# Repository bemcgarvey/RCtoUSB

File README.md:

# RCtoUSB - Wireless Joystick Dongle for RC flight sims
 
Allows an inexpensive Spektrum sattelite receiver to connect to a computer via usb as a joystick.
Works with most RC flight sims such as RealFlight 9.5

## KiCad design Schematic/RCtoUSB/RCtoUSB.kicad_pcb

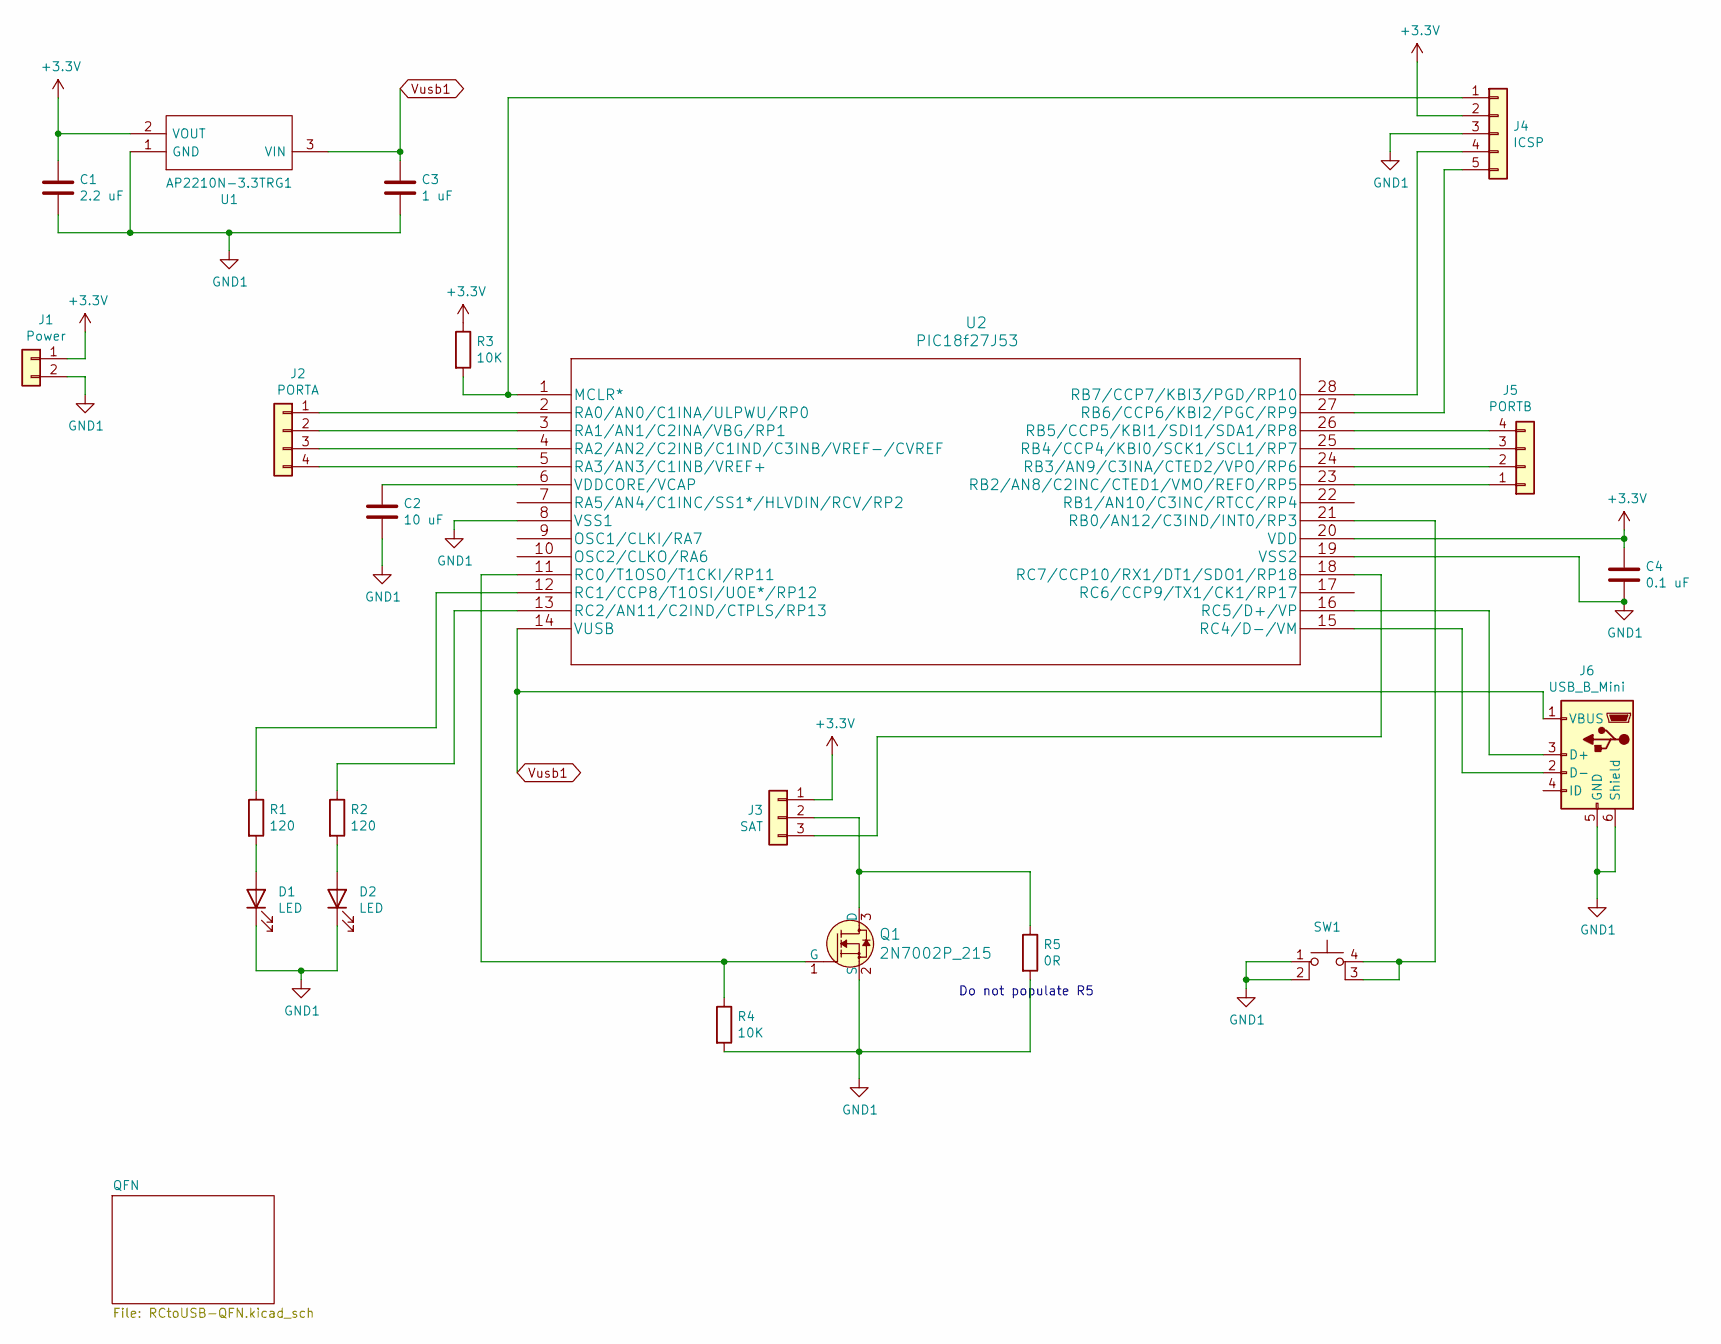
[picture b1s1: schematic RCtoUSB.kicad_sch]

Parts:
C1: 2.2 uF; C_0805_2012Metric
C2: 10 uF; C_0805_2012Metric
C3: 1 uF; C_0805_2012Metric
C4: 0.1 uF; C_0805_2012Metric
D1, D2: LED; LED_0805_2012Metric
J1: Power; PinSocket_1x02_P2.54mm_Vertical
J2: PORTA; PinSocket_1x04_P2.54mm_Vertical
J3: SAT; JST_ZH_B3B-ZR_1x03_P1.50mm_Vertical
J4: ICSP; PinHeader_1x05_P2.54mm_Vertical
J5: PORTB; PinSocket_1x04_P2.54mm_Vertical
J6: USB_B_Mini; USB_Mini-B_Wuerth_65100516121_Horizontal
Q1: 2N7002P_215; SOT-23-3; MPN 2N7002P,215; Digi-Key_PN 1727-4692-1-ND
R1, R2: 120; R_0805_2012Metric
R3, R4: 10K; R_0805_2012Metric
R5: 0R; R_0805_2012Metric
SW1: SW_MEC_5E; FSM16JH
U1: AP2210N-3.3TRG1; SOT95P280X145-3N; Mouser Part Number 621-AP2210N-3.3TRG1
U2: PIC18f27J53; pic18f27j53-i&slash_so

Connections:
GND1: C1.2, C2.2, C3.2, C4.2, D1.1 (K), D2.1 (K), J1.2, J4.3, J6.5 (GND), J6.6 (Shield), Q1.2 (S), R4.2, R5.2, SW1.1, SW1.2, U1.1 (GND), U2.8 (VSS1), U2.19 (VSS2); also elsewhere on the board
unnamed: C2.1, U2.6 (VDDCORE/VCAP)
unnamed: D1.2 (A), R1.2
unnamed: D2.2 (A), R2.2
unnamed: J2.1, U2.2 (RA0/AN0/C1INA/ULPWU/RP0)
unnamed: J2.2, U2.3 (RA1/AN1/C2INA/VBG/RP1)
unnamed: J2.3, U2.4 (RA2/AN2/C2INB/C1IND/C3INB/VREF-/CVREF)
unnamed: J2.4, U2.5 (RA3/AN3/C1INB/VREF+)
unnamed: J3.2, Q1.3 (D), R5.1
unnamed: J3.3, U2.18 (RC7/CCP10/RX1/DT1/SDO1/RP18)
unnamed: J4.1, R3.2, U2.1 (MCLR*)
unnamed: J4.4, U2.28 (RB7/CCP7/KBI3/PGD/RP10)
unnamed: J4.5, U2.27 (RB6/CCP6/KBI2/PGC/RP9)
unnamed: J5.1, U2.23 (RB2/AN8/C2INC/CTED1/VMO/REFO/RP5)
unnamed: J5.2, U2.24 (RB3/AN9/C3INA/CTED2/VPO/RP6)
unnamed: J5.3, U2.25 (RB4/CCP4/KBI0/SCK1/SCL1/RP7)
unnamed: J5.4, U2.26 (RB5/CCP5/KBI1/SDI1/SDA1/RP8)
unnamed: J6.2 (D-), U2.15 (RC4/D-/VM)
unnamed: J6.3 (D+), U2.16 (RC5/D+/VP)
unnamed: Q1.1 (G), R4.1, U2.11 (RC0/T1OSO/T1CKI/RP11)
unnamed: R1.1, U2.12 (RC1/CCP8/T1OSI/UOE*/RP12)
unnamed: R2.1, U2.13 (RC2/AN11/C2IND/CTPLS/RP13)
unnamed 38: SW1.3 (K), SW1.4 (A), U2.21 (RB0/AN12/C3IND/INT0/RP3); also elsewhere on the board
Vusb1: C3.1, J6.1 (VBUS), U1.3 (VIN), U2.14 (VUSB)

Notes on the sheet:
Do not populate R5

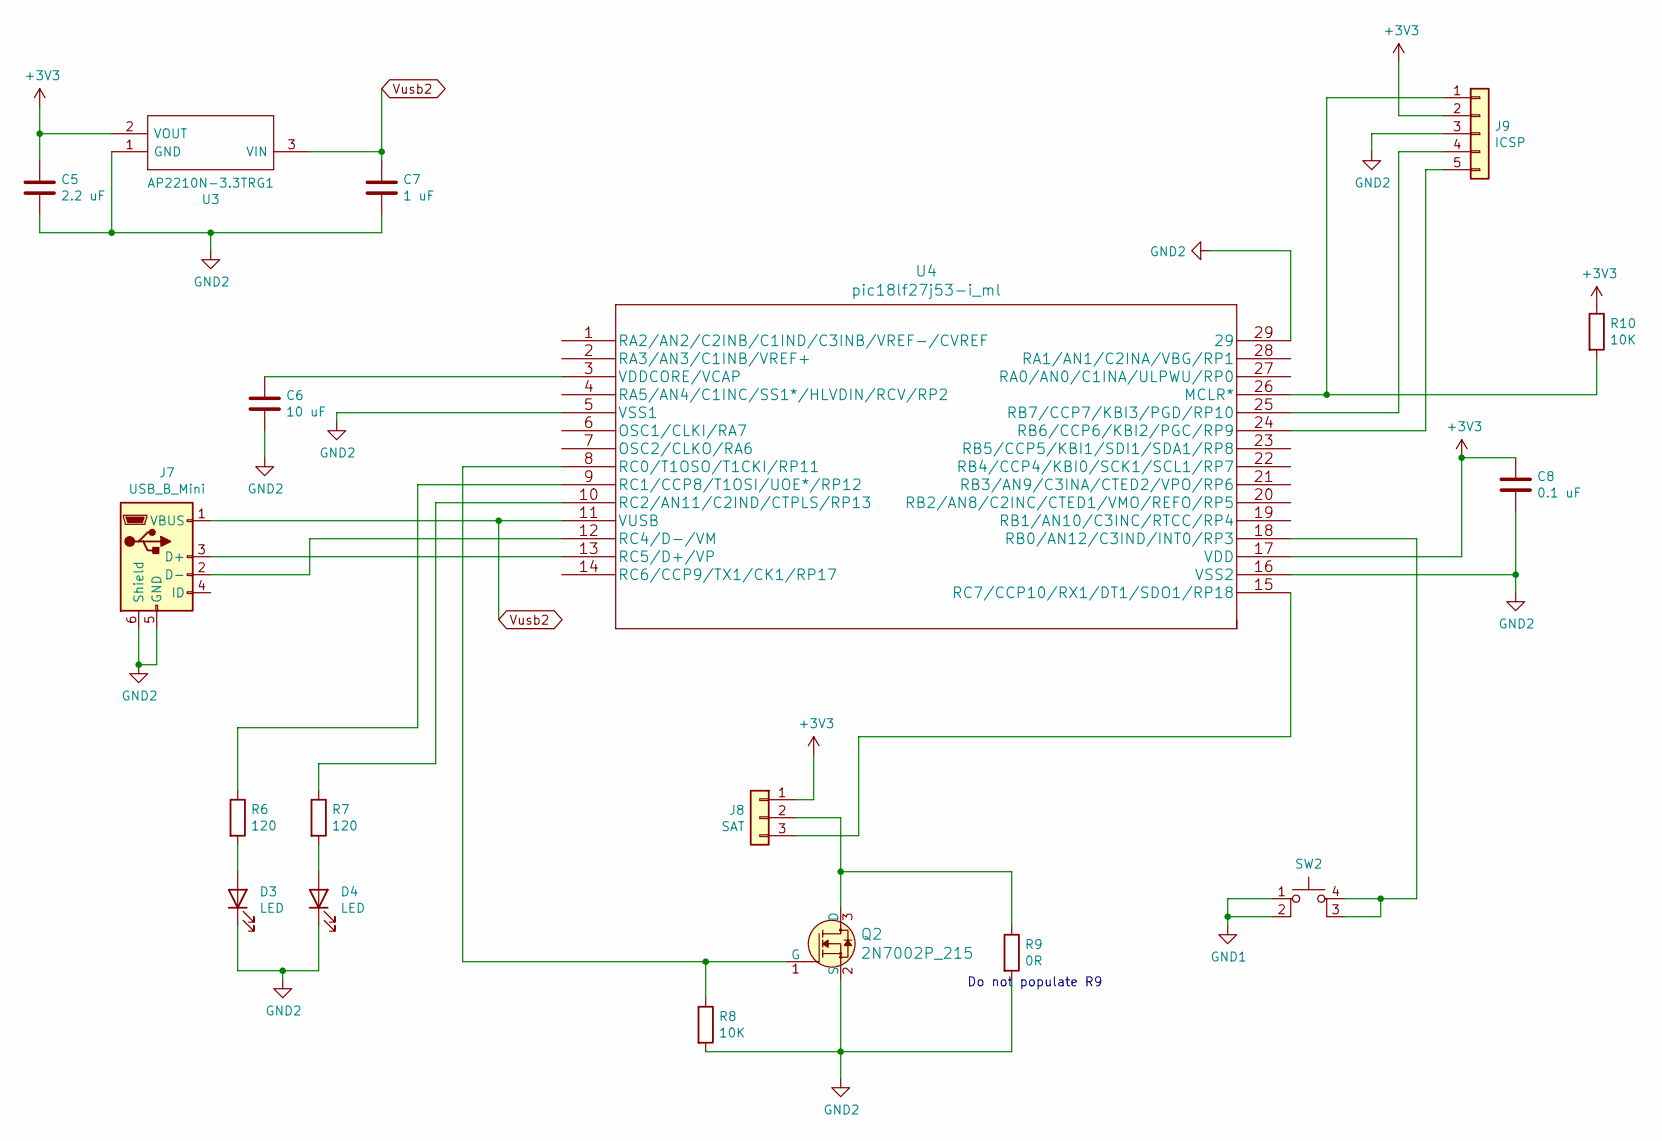
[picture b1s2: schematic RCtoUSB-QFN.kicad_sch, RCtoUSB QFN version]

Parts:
C5: 2.2 uF; C_0603_1608Metric
C6: 10 uF; C_0603_1608Metric
C7: 1 uF; C_0603_1608Metric
C8: 0.1 uF; C_0603_1608Metric
D3, D4: LED; LED_0603_1608Metric
J7: USB_B_Mini; USB_Mini-B_Wuerth_65100516121_Horizontal
J8: SAT; JST_ZH_B3B-ZR_1x03_P1.50mm_Vertical
J9: ICSP; PinHeader_1x05_P2.54mm_Vertical
Q2: 2N7002P_215; SOT-23-3; MPN 2N7002P,215; Digi-Key_PN 1727-4692-1-ND
R6, R7: 120; R_0603_1608Metric
R8, R10: 10K; R_0603_1608Metric
R9: 0R; R_0603_1608Metric
SW2: SW_MEC_5E; FSM16JH
U3: AP2210N-3.3TRG1; SOT95P280X145-3N; Mouser Part Number 621-AP2210N-3.3TRG1
U4: pic18lf27j53-i_ml; pic18lf27j53-i&slash_ml

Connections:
GND2: C5.2, C6.2, C7.2, C8.2, D3.1 (K), D4.1 (K), J7.5 (GND), J7.6 (Shield), J9.3, Q2.2 (S), R8.2, R9.2, U3.1 (GND), U4.5 (VSS1), U4.16 (VSS2), U4.29; also elsewhere on the board
unnamed: C6.1, U4.3 (VDDCORE/VCAP)
unnamed: D3.2 (A), R6.2
unnamed: D4.2 (A), R7.2
unnamed: J7.2 (D-), U4.12 (RC4/D-/VM)
unnamed: J7.3 (D+), U4.13 (RC5/D+/VP)
unnamed: J8.2, Q2.3 (D), R9.1
unnamed: J8.3, U4.15 (RC7/CCP10/RX1/DT1/SDO1/RP18)
unnamed: J9.1, R10.2, U4.26 (MCLR*)
unnamed: J9.4, U4.25 (RB7/CCP7/KBI3/PGD/RP10)
unnamed: J9.5, U4.24 (RB6/CCP6/KBI2/PGC/RP9)
unnamed: Q2.1 (G), R8.1, U4.8 (RC0/T1OSO/T1CKI/RP11)
unnamed: R6.1, U4.9 (RC1/CCP8/T1OSI/UOE*/RP12)
unnamed: R7.1, U4.10 (RC2/AN11/C2IND/CTPLS/RP13)
unnamed 39: SW2.3 (K), SW2.4 (A), U4.18 (RB0/AN12/C3IND/INT0/RP3); also elsewhere on the board
unnamed: SW2.1, SW2.2
Vusb2: C7.1, J7.1 (VBUS), U3.3 (VIN), U4.11 (VUSB)

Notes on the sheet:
Do not populate R9

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
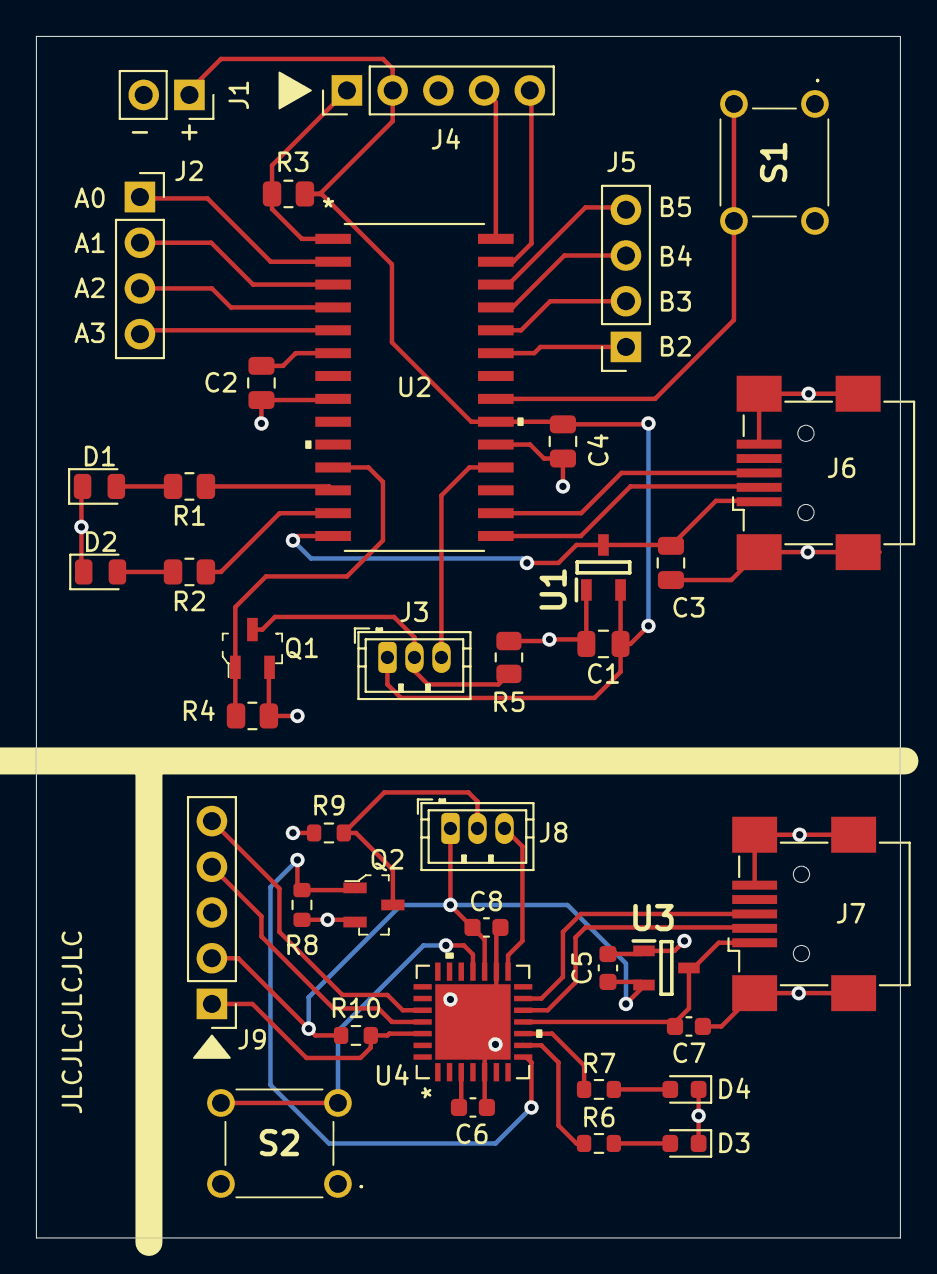
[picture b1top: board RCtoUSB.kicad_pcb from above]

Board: 2 copper layers, 48.0 x 66.8 mm, 39 parts (0 on the bottom side), 41 nets.

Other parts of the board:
S1, S2: FSM16JH

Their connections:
GND1: S1.1, S1.2; also elsewhere on the board
GND2: S2.1, S2.2; also elsewhere on the board
unnamed 38: S1.3, S1.4; also elsewhere on the board
unnamed 39: S2.3, S2.4; also elsewhere on the board

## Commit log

2021-07-23 Kicad project created
2021-07-25 Initial Schematics - SOIC and QFN
2021-07-25 Added some breakout connectors to SOIC version
2021-07-26 Fixed footprints for breakout connectors
2021-07-27 PCB layout
2021-07-28 Finished schematic and pcb
2021-08-03 Changed ID pin to floating on USB connector
2021-08-03 Generated gerbers
2021-08-20 Working joystick code
    Adapted from mla mouse code
2021-08-22 Working descriptor
2021-08-23 Flight Simulation Device hid descriptor
2021-08-23 Added hid tool files
2021-08-23 button and timer working
2021-08-23 Simple bind working
2021-08-24 Improvements to bind process
2021-08-25 Bind button short and long press working
2021-08-25 satellite rx working
2021-08-25 all channels working
2021-08-25 Improved button functionality
2021-08-26 Cleaned up code
2021-08-28 4 channel working
2021-08-28 7 channels working with RealFlight
2021-08-28 All channels working with RealFlight
2021-08-29 Fixed buttons. Removed long press to reset
2021-10-16 Improved switch symbol in schematic
2022-01-19 Converted to KiCad 6

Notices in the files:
parts and their libraries:
Copyright 2021 Accelerated Designs. All rights reserved.
